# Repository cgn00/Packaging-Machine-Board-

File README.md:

# Packaging Machine Controller Board Design

This repository contains the design of a controller board for a packaging machine based on the Teensy 3.5 microcontroller. The controller board allows for control of the motors, sensors, and actuators necessary for the packaging process.

## Installation

To use this controller board, the KiCAD circuit design software is required. Clone this repository and open the .pro file in KiCAD.

## Usage

The controller board is designed to be used in a packaging machine. The pins are labeled and can be easily connected to the corresponding motors, sensors, and actuators.

The firmware necessary for the operation of the packaging machine can be loaded onto the Teensy 3.5 microcontroller using the Arduino development software.

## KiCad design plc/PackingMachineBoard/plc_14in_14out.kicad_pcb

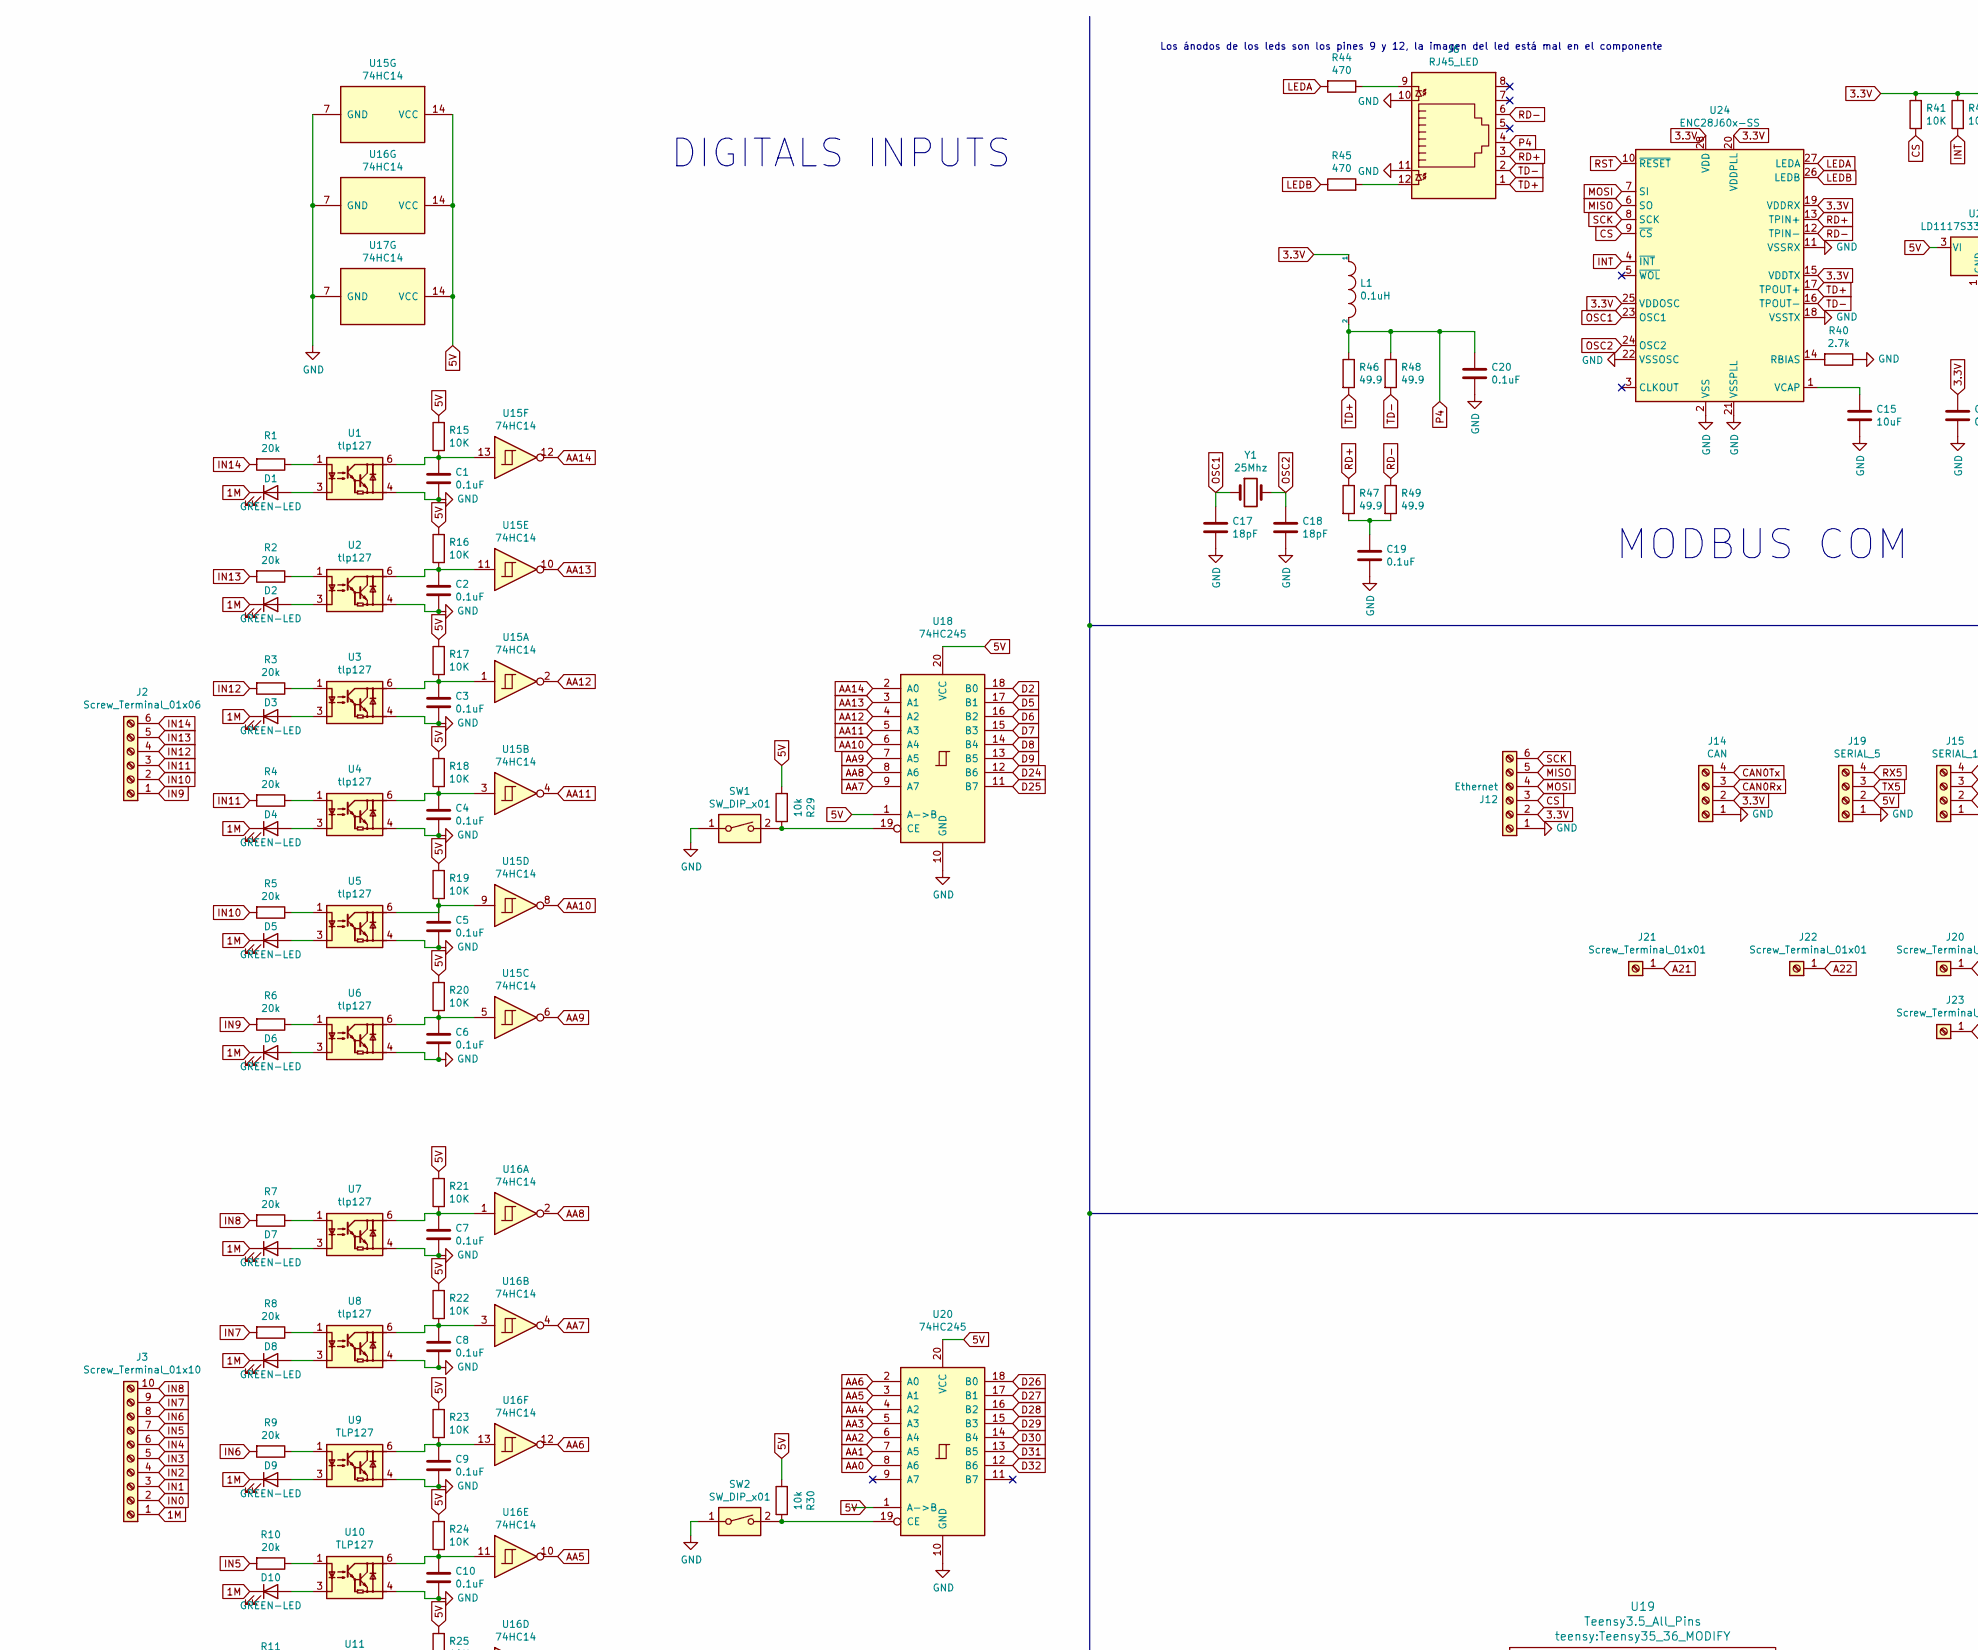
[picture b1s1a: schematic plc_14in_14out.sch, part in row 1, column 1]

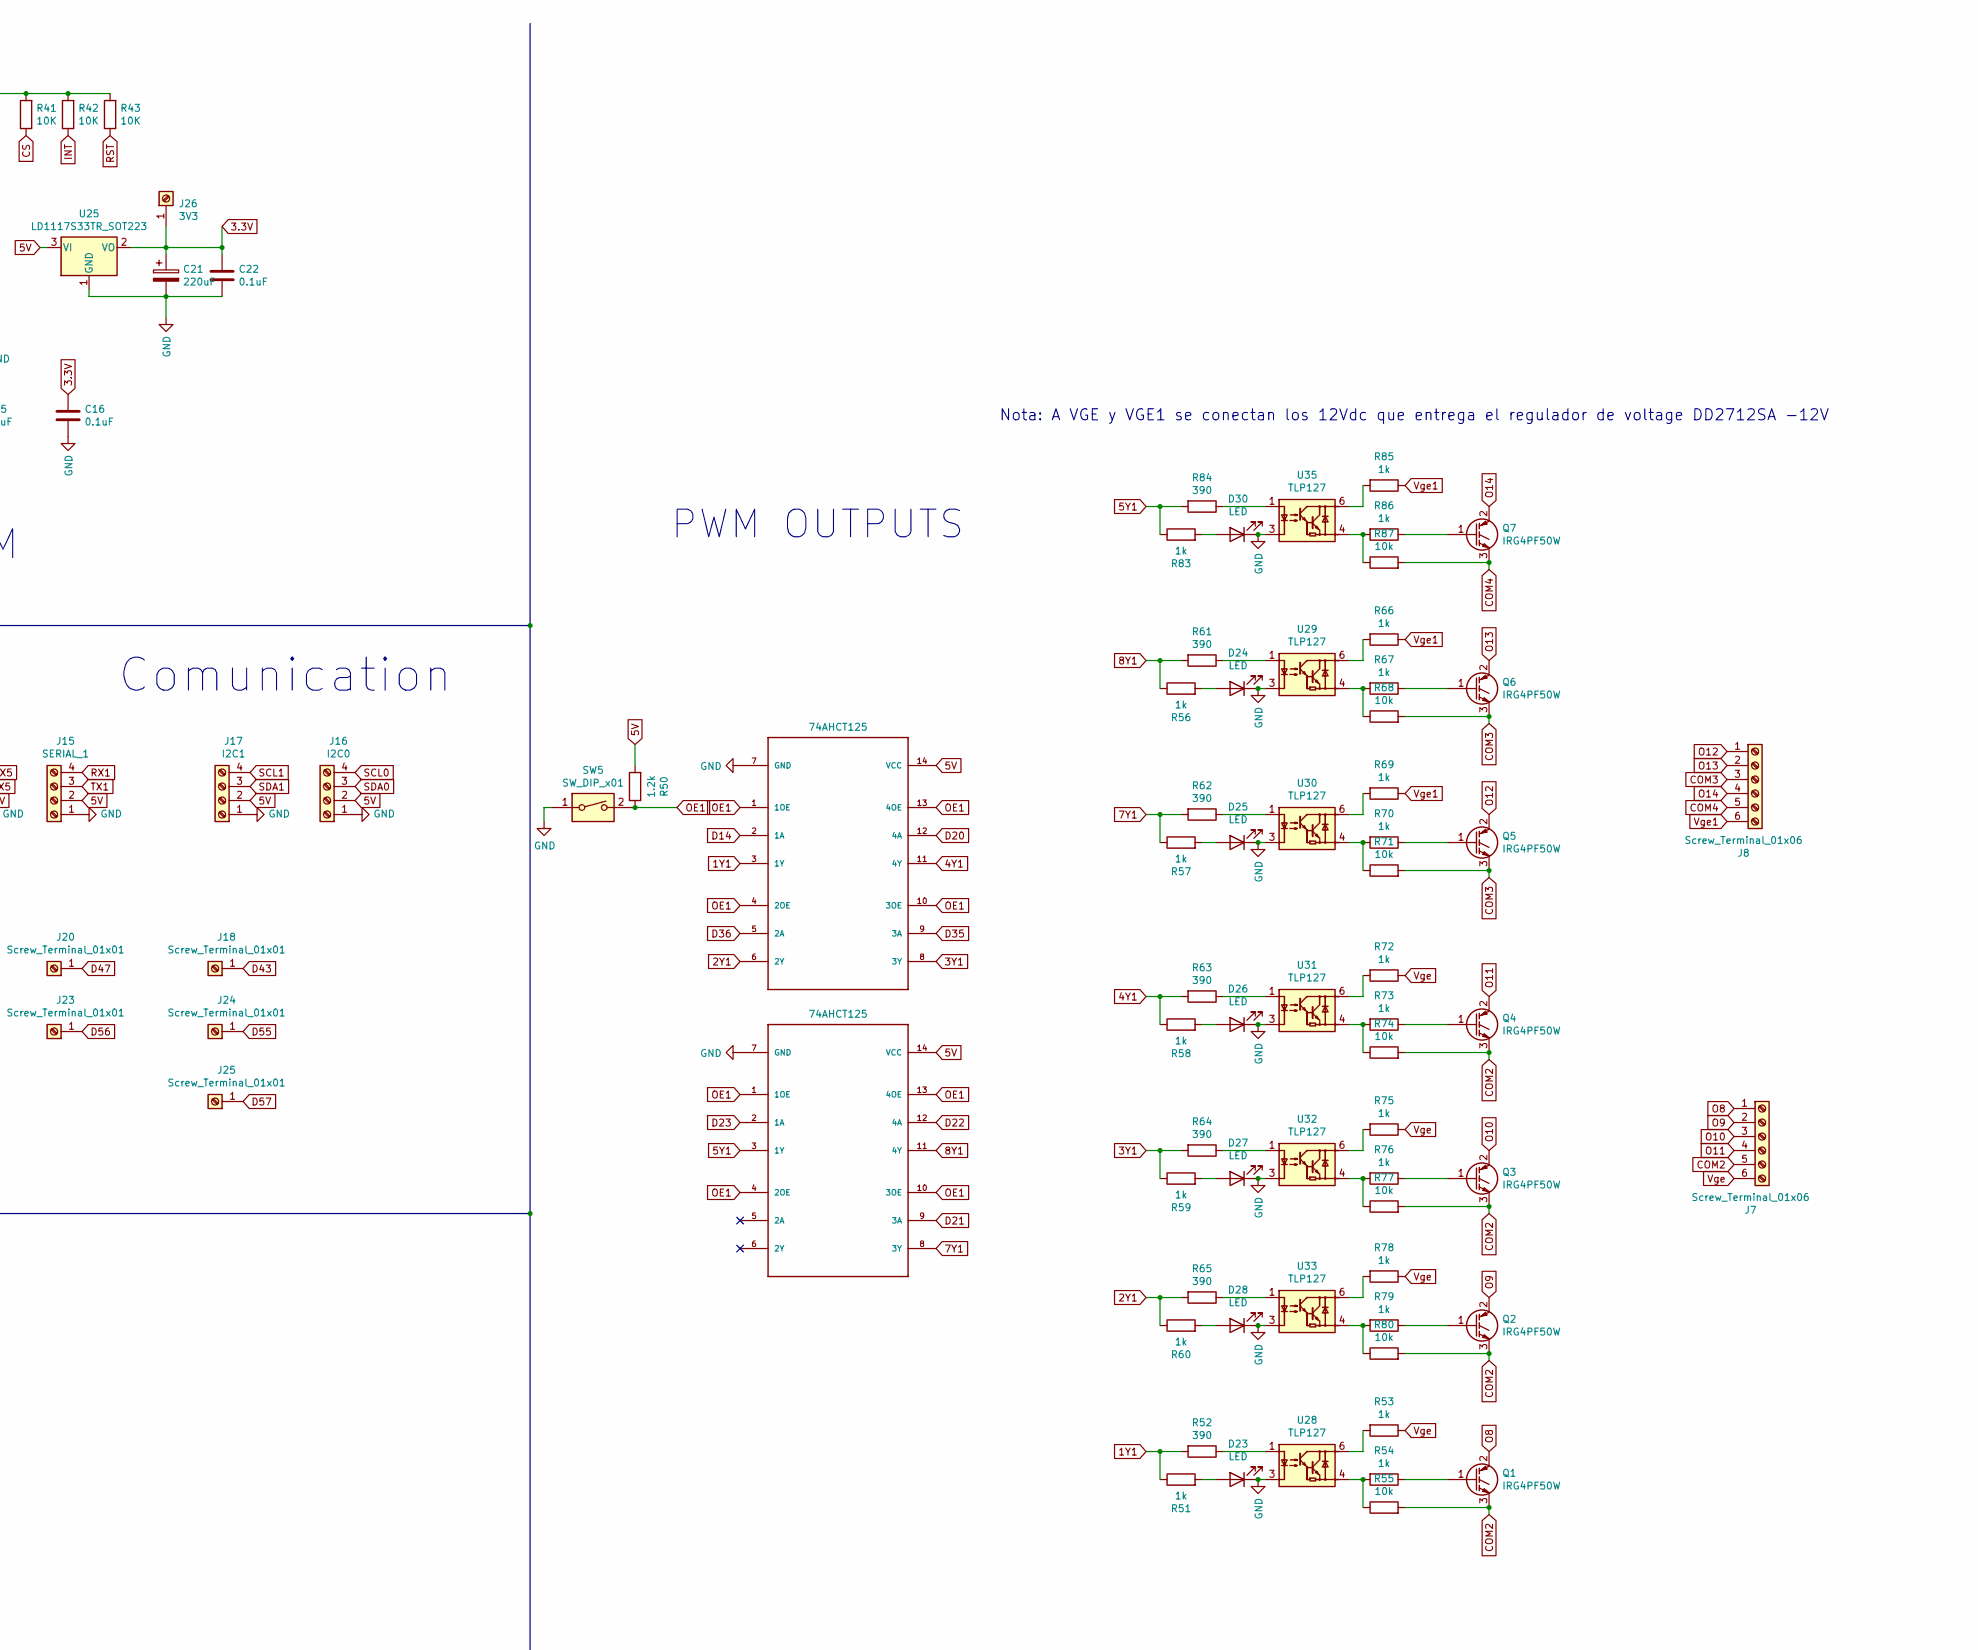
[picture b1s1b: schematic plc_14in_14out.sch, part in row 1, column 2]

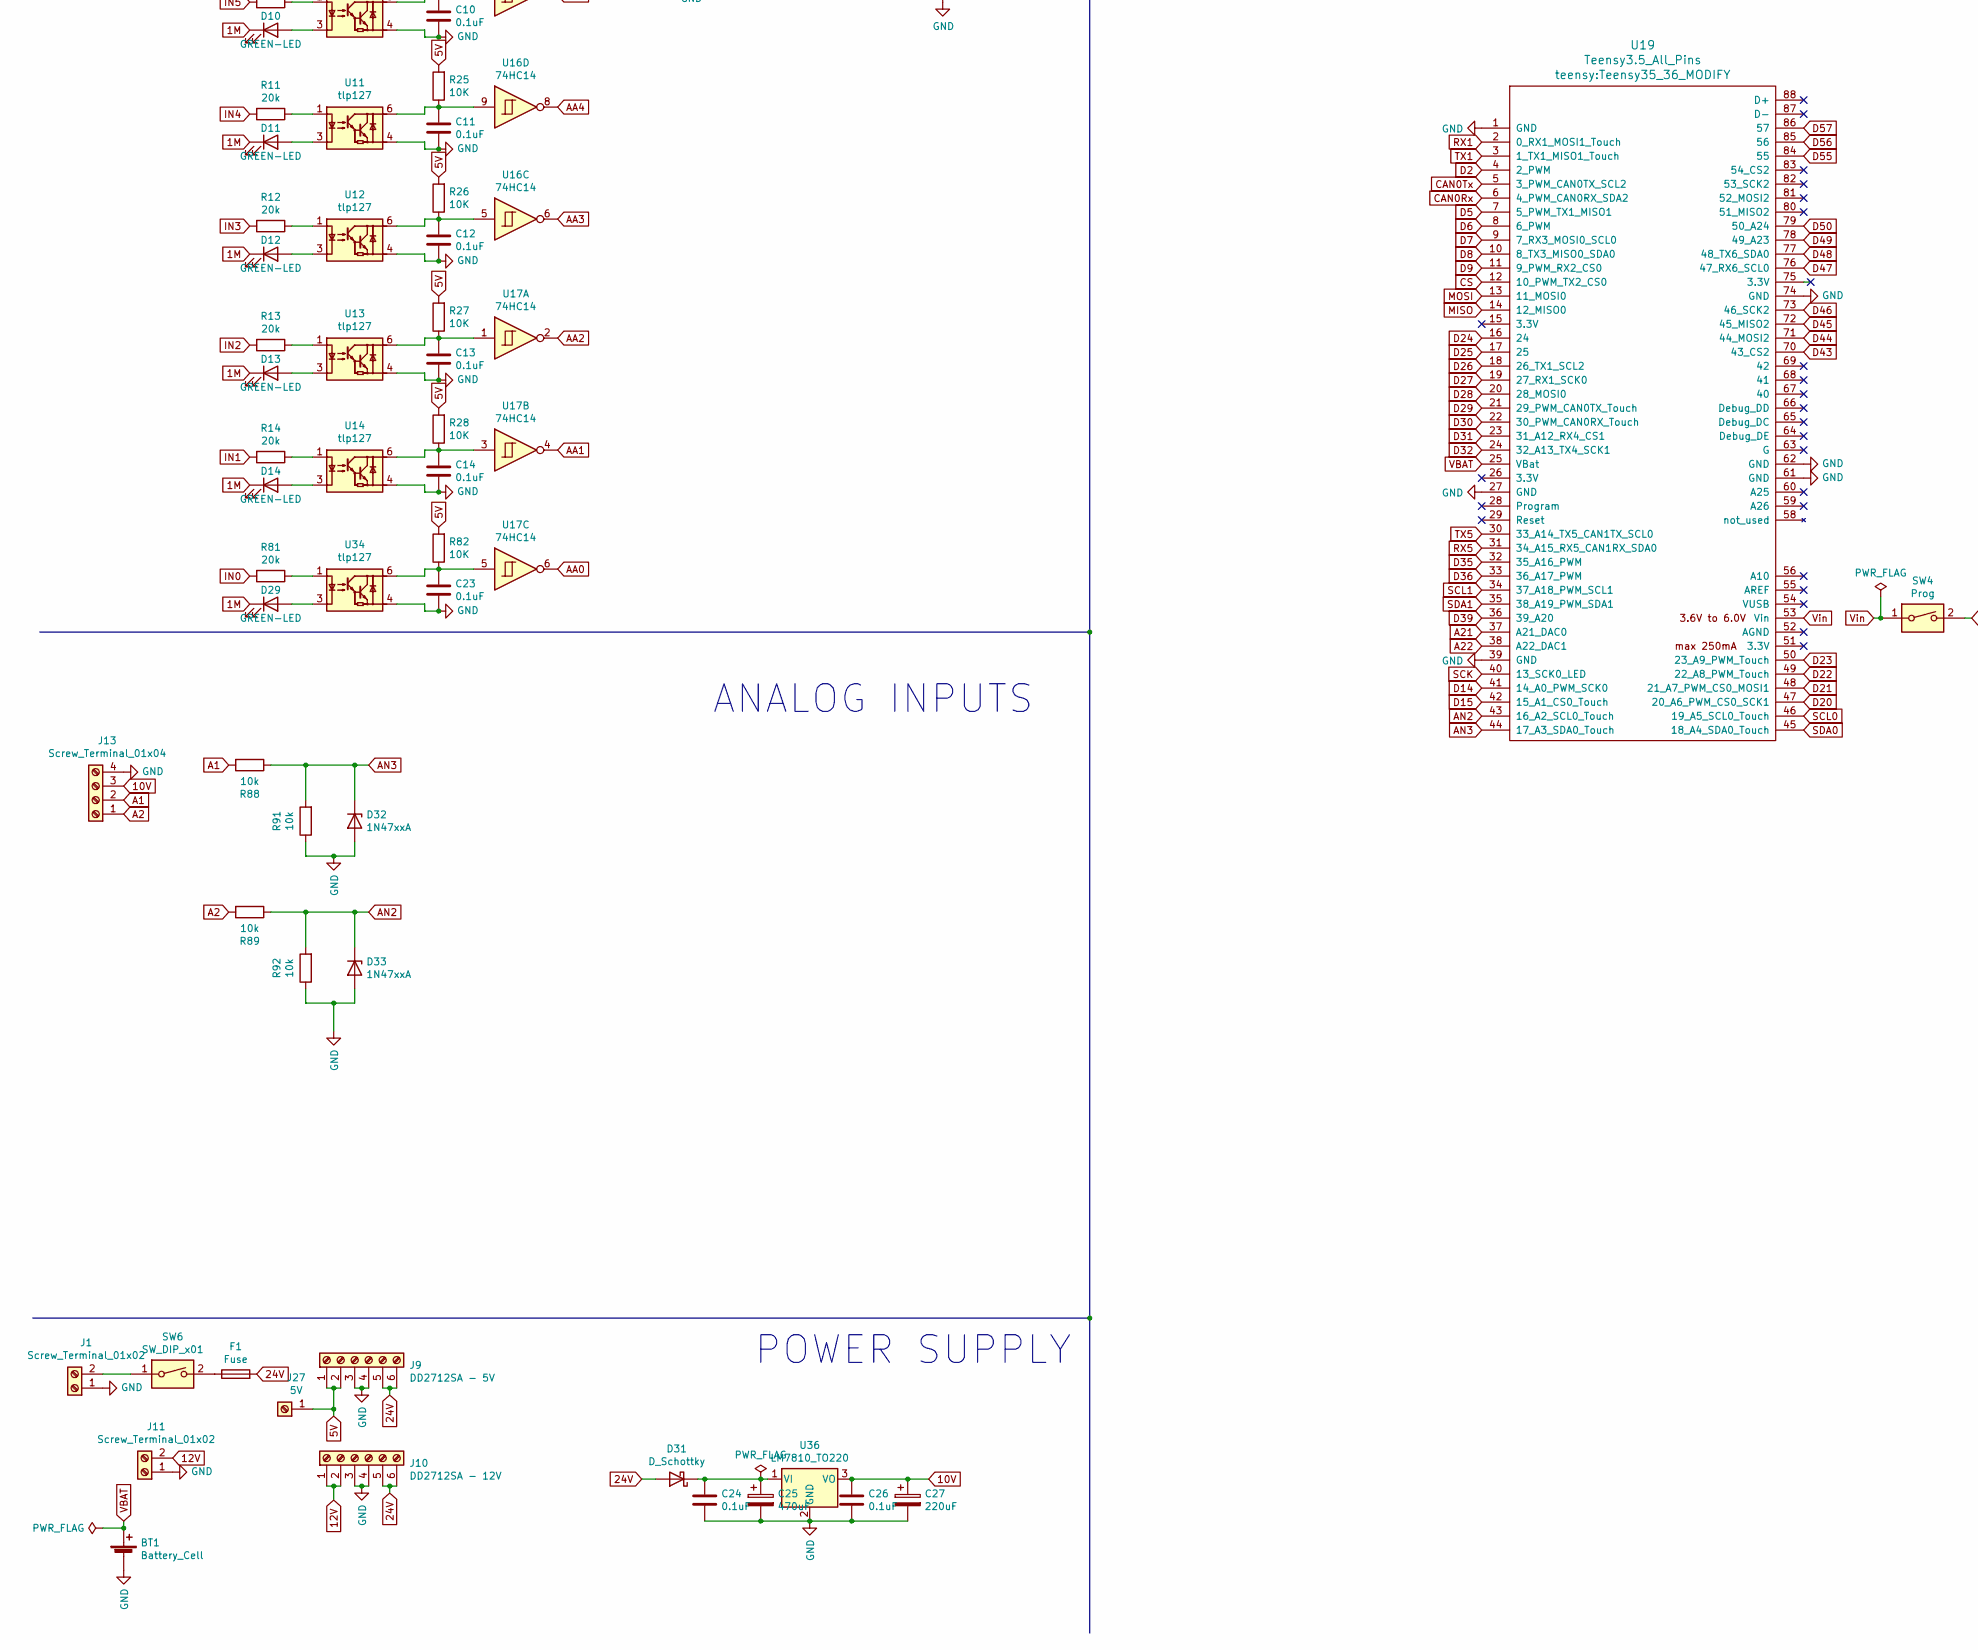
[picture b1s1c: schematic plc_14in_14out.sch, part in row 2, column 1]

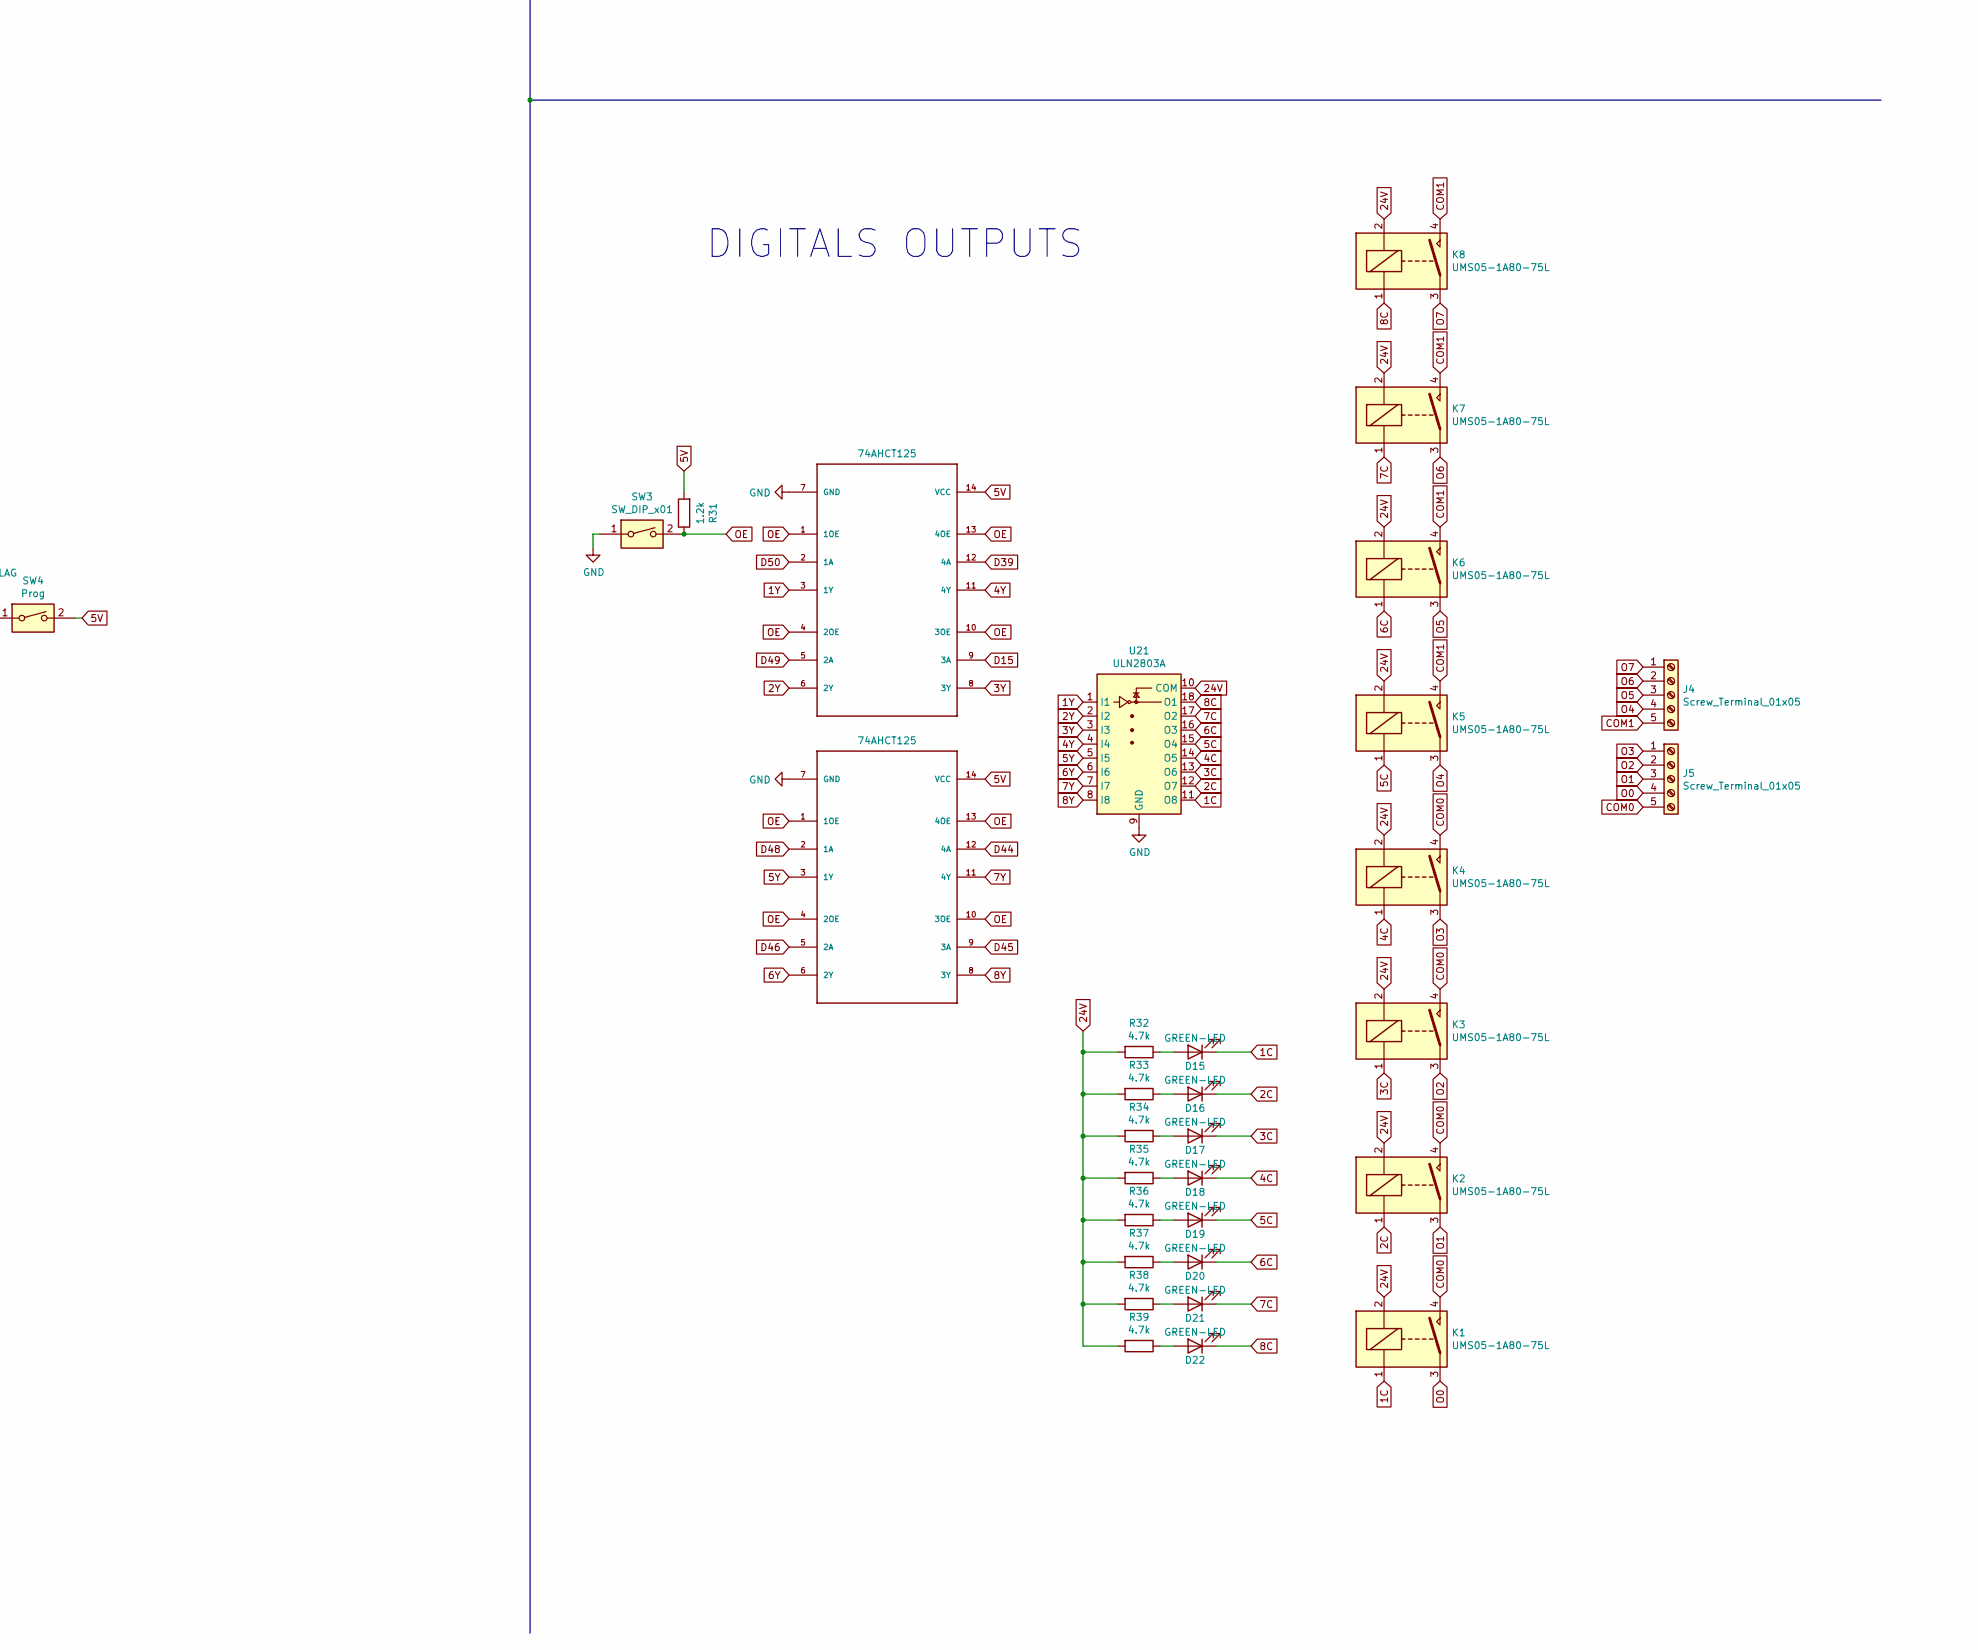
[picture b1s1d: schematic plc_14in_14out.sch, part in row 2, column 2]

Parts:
BT1: Battery_Cell; BatteryHolder_Keystone_103_1x20mm_new
C1, C2, C3, C4, C5, C6, C7, C8, C9, C10, C11, C12, C13, C14, C23, C24, C26: 0.1uF; C_1206_3216Metric
C15: 10uF; C_0805_2012Metric_Pad1.18x1.45mm_HandSolder
C16: 0.1uF; C_0603_1608Metric_Pad1.08x0.95mm_HandSolder
C17, C18: 18pF; C_0603_1608Metric
C19, C20: 0.1uF; C_0805_2012Metric_Pad1.18x1.45mm_HandSolder
C21, C27: 220uF; CP_Elec_6.3x7.7
C22: 0.1uF; C_0805_2012Metric
C25: 470uF; C_Radial_D8.0mm_H11.5mm_P3.50mm
D1, D2, D3, D4, D5, D6, D7, D8, D9, D10, D11, D12, D13, D14, D15, D16, D17, D18, D19, D20, D21, D22, D29: GREEN-LED; LED_1206_3216Metric_Castellated
D23, D24, D25, D26, D27, D28, D30: LED; LED_1206_3216Metric_Castellated
D31: D_Schottky; D_SMA_Handsoldering
D32, D33: 1N47xxA; D_DO-41_SOD81_P10.16mm_Horizontal
F1: Fuse; Fuse_2920_7451Metric_Castellated
J1, J11: Screw_Terminal_01x02; Altech_AK300_1x02_P5.00mm_45-Degree
J2, J7, J8: Screw_Terminal_01x06; Altech_AK300_1x06_P5.00mm_45-Degree
J3: Screw_Terminal_01x10; Altech_AK300_1x10_P5.00mm_45-Degree
J4, J5: Screw_Terminal_01x05; Altech_AK300_1x05_P5.00mm_45-Degree
J6: RJ45_LED; RJ45_Hanrun_HR911105A
J9: DD2712SA - 5V; PinSocket_1x06_P2.54mm_Vertical
J10: DD2712SA - 12V; PinSocket_1x06_P2.54mm_Vertical
J12: Ethernet; PinHeader_1x06_P2.54mm_Vertical
J13: Screw_Terminal_01x04; Altech_AK300_1x04_P5.00mm_45-Degree
J14: CAN; PinHeader_1x04_P2.54mm_Vertical
J15: SERIAL_1; PinHeader_1x04_P2.54mm_Vertical
J16: I2C0; PinHeader_1x04_P2.54mm_Vertical
J17: I2C1; PinHeader_1x04_P2.54mm_Vertical
J18, J20, J21, J22, J23, J24, J25: Screw_Terminal_01x01; PinHeader_1x01_P2.54mm_Vertical
J19: SERIAL_5; PinHeader_1x04_P2.54mm_Vertical
J26: 3V3; PinHeader_1x01_P2.54mm_Vertical
J27: 5V; PinHeader_1x01_P2.54mm_Vertical
K1, K2, K3, K4, K5, K6, K7, K8: UMS05-1A80-75L; Relay_SPST_TE_PCN-1xxD3MHZ
L1: 0.1uH; L_0805_2012Metric_Pad1.15x1.40mm_HandSolder
Q1, Q2, Q3, Q4, Q5, Q6, Q7: IRG4PF50W; TO-252-2
R1, R2, R3, R4, R5, R6, R7, R8, R9, R10, R11, R12, R13, R14, R81: 20k; R_1206_3216Metric_Pad1.30x1.75mm_HandSolder
R15, R16, R17, R18, R19, R20, R21, R22, R23, R24, R25, R26, R27, R28, R41, R42, R43, R82: 10K; R_0603_1608Metric
R29, R30: 10k; R_0603_1608Metric
R31, R50: 1.2k; R_1206_3216Metric_Pad1.30x1.75mm_HandSolder
R32, R33, R34, R35, R36, R37, R38, R39: 4.7k; R_1206_3216Metric_Pad1.30x1.75mm_HandSolder
R40: 2.7k; R_0603_1608Metric
R44, R45: 470; R_0603_1608Metric
R46, R47, R48, R49: 49.9; R_0805_2012Metric_Pad1.20x1.40mm_HandSolder
R51, R56, R57, R58, R59, R60, R83: 1k; R_0603_1608Metric
R52, R61, R62, R63, R64, R65, R84: 390; R_0603_1608Metric_Pad0.98x0.95mm_HandSolder
R53, R54, R66, R67, R69, R70, R72, R73, R75, R76, R78, R79, R85, R86: 1k; R_0805_2012Metric_Pad1.20x1.40mm_HandSolder
R55, R68, R71, R74, R77, R80, R87: 10k; R_0805_2012Metric_Pad1.20x1.40mm_HandSolder
R88, R89, R91, R92: 10k; R_1206_3216Metric
SW1, SW2, SW3, SW5: SW_DIP_x01; PinHeader_1x02_P2.54mm_Vertical
SW4: Prog; PinHeader_1x02_P2.54mm_Vertical
SW6: SW_DIP_x01; SW_DIP_SPSTx01_Slide_9.78x4.72mm_W7.62mm_P2.54mm
U1, U2, U3, U4, U5, U6, U7, U8, U11, U12, U13, U14, U34: tlp127; MFSOP6-4_4.4x3.6mm_P1.27mm
U9, U10, U28, U29, U30, U31, U32, U33, U35: TLP127; MFSOP6-4_4.4x3.6mm_P1.27mm
U15, U16: 74HC14
U17: 74HC14; SOIC-14_3.9x8.7mm_P1.27mm
U18, U20: 74HC245; SO-20_12.8x7.5mm_P1.27mm
U19: Teensy3.5_All_Pins; Teensy35_36_MODIFY
U21: ULN2803A; SOP-18_7x12.5mm_P1.27mm
U22, U23, U26, U27: 74AHCT125; SOIC-14_3.9x8.7mm_P1.27mm
U24: ENC28J60x-SS; SSOP-28_5.3x10.2mm_P0.65mm
U25: LD1117S33TR_SOT223; SOT-223-3_TabPin2
U36: LM7810_TO220; TO-220-3_Vertical
Y1: 25Mhz; Crystal_HC49-4H_Vertical

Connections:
1C: D15.1 (K), K1.1, U21.11 (O8)
1M: D1.1 (K), D2.1 (K), D3.1 (K), D4.1 (K), D5.1 (K), D6.1 (K), D7.1 (K), D8.1 (K), D9.1 (K), D10.1 (K), D11.1 (K), D12.1 (K), D13.1 (K), D14.1 (K), D29.1 (K), J3.1
1Y: U21.1 (I1), U23.3 (1Y)
1Y1: R51.1, R52.2, U26.3 (1Y)
2C: D16.1 (K), K2.1, U21.12 (O7)
2Y: U21.2 (I2), U23.6 (2Y)
2Y1: R60.1, R65.2, U26.6 (2Y)
3.3V: C16.1, C21.1, C22.1, J12.2, J14.2, J26.1, L1.1, R41.2, R42.2, R43.2, U24.15 (VDDTX), U24.19 (VDDRX), U24.20 (VDDPLL), U24.25 (VDDOSC), U24.28 (VDD), U25.2 (VO)
3C: D17.1 (K), K3.1, U21.13 (O6)
3Y: U21.3 (I3), U23.8 (3Y)
3Y1: R59.1, R64.2, U26.8 (3Y)
4C: D18.1 (K), K4.1, U21.14 (O5)
4Y: U21.4 (I4), U23.11 (4Y)
4Y1: R58.1, R63.2, U26.11 (4Y)
5C: D19.1 (K), K5.1, U21.15 (O4)
5V: J9.1, J9.2, J15.2, J16.2, J17.2, J19.2, J27.1, R15.2, R16.2, R17.2, R18.2, R19.2, R20.2, R21.2, R22.2, R23.2, R24.2, R25.2, R26.2, R27.2, R28.2, R29.2, R30.2, R31.2, R50.2, R82.2, SW4.2, U15.14 (VCC), U16.14 (VCC), U17.14 (VCC), U18.1 (A->B), U18.20 (VCC), U20.1 (A->B), U20.20 (VCC), U22.14 (VCC), U23.14 (VCC), U25.3 (VI), U26.14 (VCC), U27.14 (VCC)
5Y: U21.5 (I5), U22.3 (1Y)
5Y1: R83.1, R84.2, U27.3 (1Y)
6C: D20.1 (K), K6.1, U21.16 (O3)
6Y: U21.6 (I6), U22.6 (2Y)
7C: D21.1 (K), K7.1, U21.17 (O2)
7Y: U21.7 (I7), U22.11 (4Y)
7Y1: R57.1, R62.2, U27.8 (3Y)
8C: D22.1 (K), K8.1, U21.18 (O1)
8Y: U21.8 (I8), U22.8 (3Y)
8Y1: R56.1, R61.2, U27.11 (4Y)
10V: C26.1, C27.1, J13.3, U36.3 (VO)
12V: J10.1, J10.2, J11.2
24V: D31.2 (A), F1.2, J9.5, J9.6, J10.5, J10.6, K1.2, K2.2, K3.2, K4.2, K5.2, K6.2, K7.2, K8.2, R32.2, R33.2, R34.2, R35.2, R36.2, R37.2, R38.2, R39.2, U21.10 (COM)
A1: J13.2, R88.2
A2: J13.1, R89.2
A21: J21.1, U19.37 (A21_DAC0)
A22: J22.1, U19.38 (A22_DAC1)
AA0: U17.6, U20.8 (A6)
AA1: U17.4, U20.7 (A5)
AA2: U17.2, U20.6 (A4)
AA3: U16.6, U20.5 (A3)
AA4: U16.8, U20.4 (A2)
AA5: U16.10, U20.3 (A1)
AA6: U16.12, U20.2 (A0)
AA7: U16.4, U18.9 (A7)
AA8: U16.2, U18.8 (A6)
AA9: U15.6, U18.7 (A5)
AA10: U15.8, U18.6 (A4)
AA11: U15.4, U18.5 (A3)
AA12: U15.2, U18.4 (A2)
AA13: U15.10, U18.3 (A1)
AA14: U15.12, U18.2 (A0)
AN2: D33.1 (K), R89.1, R92.2, U19.43 (16_A2_SCL0_Touch)
AN3: D32.1 (K), R88.1, R91.2, U19.44 (17_A3_SDA0_Touch)
CAN0Rx: J14.3, U19.6 (4_PWM_CAN0RX_SDA2)
CAN0Tx: J14.4, U19.5 (3_PWM_CAN0TX_SCL2)
COM0: J5.5, K1.4, K2.4, K3.4, K4.4
COM1: J4.5, K5.4, K6.4, K7.4, K8.4
COM2: J7.5, Q1.3 (E), Q2.3 (E), Q3.3 (E), Q4.3 (E), R55.2, R74.2, R77.2, R80.2
COM3: J8.3, Q5.3 (E), Q6.3 (E), R68.2, R71.2
COM4: J8.5, Q7.3 (E), R87.2
CS: J12.3, R41.1, U19.12 (10_PWM_TX2_CS0), U24.9 (~CS)
D2: U18.18 (B0), U19.4 (2_PWM)
D5: U18.17 (B1), U19.7 (5_PWM_TX1_MISO1)
D6: U18.16 (B2), U19.8 (6_PWM)
D7: U18.15 (B3), U19.9 (7_RX3_MOSI0_SCL0)
D8: U18.14 (B4), U19.10 (8_TX3_MISO0_SDA0)
D9: U18.13 (B5), U19.11 (9_PWM_RX2_CS0)
D14: U19.41 (14_A0_PWM_SCK0), U26.2 (1A)
D15: U19.42 (15_A1_CS0_Touch), U23.9 (3A)
D20: U19.47 (20_A6_PWM_CS0_SCK1), U26.12 (4A)
D21: U19.48 (21_A7_PWM_CS0_MOSI1), U27.9 (3A)
D22: U19.49 (22_A8_PWM_Touch), U27.12 (4A)
D23: U19.50 (23_A9_PWM_Touch), U27.2 (1A)
D24: U18.12 (B6), U19.16 (24)
D25: U18.11 (B7), U19.17 (25)
D26: U19.18 (26_TX1_SCL2), U20.18 (B0)
D27: U19.19 (27_RX1_SCK0), U20.17 (B1)
D28: U19.20 (28_MOSI0), U20.16 (B2)
D29: U19.21 (29_PWM_CAN0TX_Touch), U20.15 (B3)
D30: U19.22 (30_PWM_CAN0RX_Touch), U20.14 (B4)
D31: U19.23 (31_A12_RX4_CS1), U20.13 (B5)
D32: U19.24 (32_A13_TX4_SCK1), U20.12 (B6)
D35: U19.32 (35_A16_PWM), U26.9 (3A)
D36: U19.33 (36_A17_PWM), U26.5 (2A)
D39: U19.36 (39_A20), U23.12 (4A)
D43: J18.1, U19.70 (43_CS2)
D44: U19.71 (44_MOSI2), U22.12 (4A)
D45: U19.72 (45_MISO2), U22.9 (3A)
D46: U19.73 (46_SCK2), U22.5 (2A)
D47: J20.1, U19.76 (47_RX6_SCL0)
D48: U19.77 (48_TX6_SDA0), U22.2 (1A)
D49: U19.78 (49_A23), U23.5 (2A)
D50: U19.79 (50_A24), U23.2 (1A)
D55: J24.1, U19.84 (55)
D56: J23.1, U19.85 (56)
D57: J25.1, U19.86 (57)
GND: BT1.2 (-), C1.2, C2.2, C3.2, C4.2, C5.2, C6.2, C7.2, C8.2, C9.2, C10.2, C11.2, C12.2, C13.2, C14.2, C15.2, C16.2, C17.2, C18.2, C19.2, C20.2, C21.2, C22.2, C23.2, C24.2, C25.2, C26.2, C27.2, D23.1 (K), D24.1 (K), D25.1 (K), D26.1 (K), D27.1 (K), D28.1 (K), D30.1 (K), D32.2 (A), D33.2 (A), J1.1, J6.10, J6.11, J9.3, J9.4, J10.3, J10.4, J11.1, J12.1, J13.4, J14.1, J15.1, J16.1, J17.1, J19.1, R40.1, R91.1, R92.1, SW1.1, SW2.1, SW3.1, SW5.1, U1.4, U2.4, U3.4, U4.4, U5.4, U6.4, U7.4, U8.4, U9.4, U10.4, U11.4, U12.4, U13.4, U14.4, U15.7 (GND), U16.7 (GND), U17.7 (GND), U18.10 (GND), U19.1 (GND), U19.27 (GND), U19.39 (GND), U19.61 (GND), U19.62 (GND), U19.74 (GND), U20.10 (GND), U21.9 (GND), U22.7 (GND), U23.7 (GND), U24.2 (VSS), U24.11 (VSSRX), U24.18 (VSSTX), U24.21 (VSSPLL), U24.22 (VSSOSC), U25.1 (GND), U26.7 (GND), U27.7 (GND), U28.3, U29.3, U30.3, U31.3, U32.3, U33.3, U34.4, U35.3, U36.2 (GND)
IN0: J3.2, R81.2
IN1: J3.3, R14.2
IN2: J3.4, R13.2
IN3: J3.5, R12.2
IN4: J3.6, R11.2
IN5: J3.7, R10.2
IN6: J3.8, R9.2
IN7: J3.9, R8.2
IN8: J3.10, R7.2
IN9: J2.1, R6.2
IN10: J2.2, R5.2
IN11: J2.3, R4.2
IN12: J2.4, R3.2
IN13: J2.5, R2.2
IN14: J2.6, R1.2
INT: R42.1, U24.4 (~INT)
LEDA: R44.2, U24.27 (LEDA)
LEDB: R45.1, U24.26 (LEDB)
MISO: J12.5, U19.14 (12_MISO0), U24.6 (SO)
MOSI: J12.4, U19.13 (11_MOSI0), U24.7 (SI)
unnamed: C1.1, R15.1, U1.6, U15.13
unnamed: C2.1, R16.1, U2.6, U15.11
unnamed: C3.1, R17.1, U3.6, U15.1
unnamed: C4.1, R18.1, U4.6, U15.3
unnamed: C5.1, R19.1, U5.6, U15.9
unnamed: C6.1, R20.1, U6.6, U15.5
unnamed: C7.1, R21.1, U7.6, U16.1
unnamed: C8.1, R22.1, U8.6, U16.3
unnamed: C9.1, R23.1, U9.6, U16.13
unnamed: C10.1, R24.1, U10.6, U16.11
unnamed: C11.1, R25.1, U11.6, U16.9
unnamed: C12.1, R26.1, U12.6, U16.5
unnamed: C13.1, R27.1, U13.6, U17.1
unnamed: C14.1, R28.1, U14.6, U17.3
unnamed: C15.1, U24.1 (VCAP)
unnamed: C19.1, R47.2, R49.2
unnamed: C23.1, R82.1, U17.5, U34.6
unnamed: C24.1, C25.1, D31.1 (K), U36.1 (VI)
unnamed: D1.2 (A), U1.3
unnamed: D2.2 (A), U2.3
unnamed: D3.2 (A), U3.3
unnamed: D4.2 (A), U4.3
unnamed: D5.2 (A), U5.3
unnamed: D6.2 (A), U6.3
unnamed: D7.2 (A), U7.3
unnamed: D8.2 (A), U8.3
unnamed: D9.2 (A), U9.3
unnamed: D10.2 (A), U10.3
unnamed: D11.2 (A), U11.3
unnamed: D12.2 (A), U12.3
unnamed: D13.2 (A), U13.3
unnamed: D14.2 (A), U14.3
unnamed: D15.2 (A), R32.1
unnamed: D16.2 (A), R33.1
unnamed: D17.2 (A), R34.1
unnamed: D18.2 (A), R35.1
unnamed: D19.2 (A), R36.1
unnamed: D20.2 (A), R37.1
unnamed: D21.2 (A), R38.1
unnamed: D22.2 (A), R39.1
unnamed: D23.2 (A), R51.2
unnamed: D24.2 (A), R56.2
unnamed: D25.2 (A), R57.2
unnamed: D26.2 (A), R58.2
unnamed: D27.2 (A), R59.2
unnamed: D28.2 (A), R60.2
unnamed: D29.2 (A), U34.3
unnamed: D30.2 (A), R83.2
unnamed: F1.1, SW6.2
unnamed: J1.2, SW6.1
unnamed: J6.9, R44.1
unnamed: J6.12, R45.2
unnamed: Q1.1 (G), R54.1
unnamed: Q2.1 (G), R79.1
unnamed: Q3.1 (G), R76.1
unnamed: Q4.1 (G), R73.1
unnamed: Q5.1 (G), R70.1
unnamed: Q6.1 (G), R67.1
unnamed: Q7.1 (G), R86.1
unnamed: R1.1, U1.1
unnamed: R2.1, U2.1
unnamed: R3.1, U3.1
unnamed: R4.1, U4.1
unnamed: R5.1, U5.1
unnamed: R6.1, U6.1
unnamed: R7.1, U7.1
unnamed: R8.1, U8.1
unnamed: R9.1, U9.1
unnamed: R10.1, U10.1
unnamed: R11.1, U11.1
unnamed: R12.1, U12.1
unnamed: R13.1, U13.1
unnamed: R14.1, U14.1
unnamed: R29.1, SW1.2, U18.19 (CE)
unnamed: R30.1, SW2.2, U20.19 (CE)
unnamed: R40.2, U24.14 (RBIAS)
unnamed: R52.1, U28.1
unnamed: R53.2, U28.6
unnamed: R54.2, R55.1, U28.4
unnamed: R61.1, U29.1
unnamed: R62.1, U30.1
unnamed: R63.1, U31.1
unnamed: R64.1, U32.1
unnamed: R65.1, U33.1
unnamed: R66.2, U29.6
unnamed: R67.2, R68.1, U29.4
unnamed: R69.2, U30.6
unnamed: R70.2, R71.1, U30.4
unnamed: R72.2, U31.6
unnamed: R73.2, R74.1, U31.4
unnamed: R75.2, U32.6
unnamed: R76.2, R77.1, U32.4
unnamed: R78.2, U33.6
unnamed: R79.2, R80.1, U33.4
unnamed: R81.1, U34.1
unnamed: R84.1, U35.1
unnamed: R85.2, U35.6
unnamed: R86.2, R87.1, U35.4
O0: J5.4, K1.3
O1: J5.3, K2.3
O2: J5.2, K3.3
O3: J5.1, K4.3
O4: J4.4, K5.3
O5: J4.3, K6.3
O6: J4.2, K7.3
O7: J4.1, K8.3
O8: J7.1, Q1.2 (C)
O9: J7.2, Q2.2 (C)
O10: J7.3, Q3.2 (C)
O11: J7.4, Q4.2 (C)
O12: J8.1, Q5.2 (C)
O13: J8.2, Q6.2 (C)
O14: J8.4, Q7.2 (C)
OE: R31.1, SW3.2, U22.1 (1OE), U22.4 (2OE), U22.10 (3OE), U22.13 (4OE), U23.1 (1OE), U23.4 (2OE), U23.10 (3OE), U23.13 (4OE)
OE1: R50.1, SW5.2, U26.1 (1OE), U26.4 (2OE), U26.10 (3OE), U26.13 (4OE), U27.1 (1OE), U27.4 (2OE), U27.10 (3OE), U27.13 (4OE)
OSC1: C17.1, U24.23 (OSC1), Y1.1
OSC2: C18.1, U24.24 (OSC2), Y1.2
P4: C20.1, J6.4, L1.2, R46.1, R48.1
RD+: J6.3, R47.1, U24.13 (TPIN+)
RD-: J6.6, R49.1, U24.12 (TPIN-)
RST: R43.1, U24.10 (~RESET)
RX1: J15.4, U19.2 (0_RX1_MOSI1_Touch)
RX5: J19.4, U19.31 (34_A15_RX5_CAN1RX_SDA0)
SCK: J12.6, U19.40 (13_SCK0_LED), U24.8 (SCK)
SCL0: J16.4, U19.46 (19_A5_SCL0_Touch)
SCL1: J17.4, U19.34 (37_A18_PWM_SCL1)
SDA0: J16.3, U19.45 (18_A4_SDA0_Touch)
SDA1: J17.3, U19.35 (38_A19_PWM_SDA1)
TD+: J6.1, R46.2, U24.17 (TPOUT+)
TD-: J6.2, R48.2, U24.16 (TPOUT-)
TX1: J15.3, U19.3 (1_TX1_MISO1_Touch)
TX5: J19.3, U19.30 (33_A14_TX5_CAN1TX_SCL0)
VBAT: BT1.1 (+), U19.25 (VBat)
Vge: J7.6, R53.1, R72.1, R75.1, R78.1
Vge1: J8.6, R66.1, R69.1, R85.1
Vin: SW4.1, U19.53 (Vin)

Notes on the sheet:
Los ánodos de los leds son los pines 9 y 12, la imagen del led está mal en el componente
MODBUS COM
DIGITALS INPUTS
DIGITALS OUTPUTS
PWM OUTPUTS
POWER SUPPLY
ANALOG INPUTS
Comunication
Nota: A VGE y VGE1 se conectan los 12Vdc que entrega el regulador de voltage DD2712SA -12V

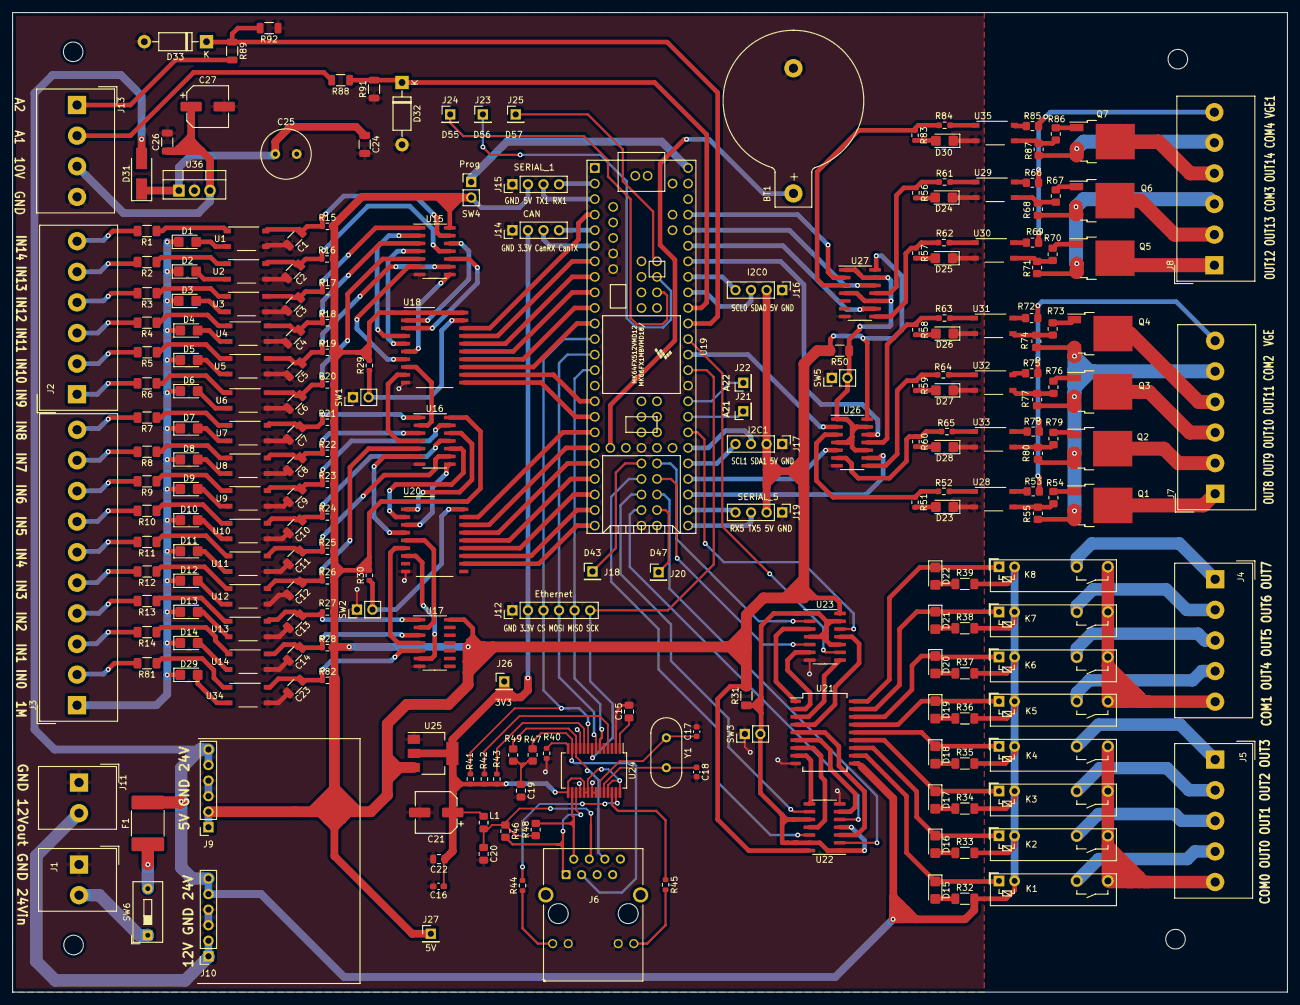
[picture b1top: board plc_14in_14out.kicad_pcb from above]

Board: 2 copper layers, 208.3 x 160.0 mm, 239 parts (0 on the bottom side), 250 nets.
